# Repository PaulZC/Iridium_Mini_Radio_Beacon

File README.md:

# Iridium_Mini_Radio_Beacon

An 80g version of the [Iridium 9603N Beacon](https://github.com/PaulZC/Iridium_9603_Beacon) with eRIC4/9 radio support
.

Suitable for high altitude ballooning and many other asset tracking applications.

This version is powered by a single Energiser® Ultimate Lithium L522 (PP3) 9V battery, which helps keep the design as compact as possible.

If you want to keep the size and weight as low as possible, and don't need a radio link, have a look at
the [Iridium 9603N Mini Beacon](https://github.com/PaulZC/Iridium_9603N_Mini_Beacon) instead.

The Iridium 9603N transceiver and u-blox MAX-M8Q GNSS receiver share a single Maxtena M1600HCT-P-SMA antenna, again to keep the weight as low as possible.
The antenna sharing circuit has been flight tested on the [Iridium 9603N Solar Beacon](https://github.com/PaulZC/Iridium_9603N_Solar_Beacon).

Full details of how to track your beacon via the Rock7 RockBLOCK Gateway are included in the
[Iridium 9603N Beacon repo](https://github.com/PaulZC/Iridium_9603_Beacon/blob/master/RockBLOCK.md).

[ASSEMBLY.md](https://github.com/PaulZC/Iridium_Mini_Radio_Beacon/blob/master/ASSEMBLY.md) describes how to assemble the PCB.

The [Arduino folder](https://github.com/PaulZC/Iridium_Mini_Radio_Beacon/tree/master/Arduino) contains the code for the SAMD21 processor.
You can find the [programming instructions](https://github.com/PaulZC/Iridium_9603_Beacon/blob/master/LEARN.md#how-do-i-install-the-atsamd21g18-bootloader)
and [upload instructions](https://github.com/PaulZC/Iridium_9603_Beacon/blob/master/LEARN.md#how-do-i-upload-the-arduino-code) in the Iridium 9603N Beacon repo.

The Eagle files are available in the [Eagle folder](https://github.com/PaulZC/Iridium_Mini_Radio_Beacon/tree/master/Eagle).

The schematic, dimensions and BOM are available [here](https://github.com/PaulZC/Iridium_Mini_Radio_Beacon/blob/master/Iridium_Mini_Radio_Beacon.pdf).

The [OpenSCAD folder](https://github.com/PaulZC/Iridium_Mini_Radio_Beacon/tree/master/OpenSCAD) contains .scad and .stl files for the 3D-printed cover.

## Licence

This project is distributed under a Creative Commons Attribution + Share-alike (BY-SA) licence.
Please refer to section 5 of the licence for the "Disclaimer of Warranties and Limitation of Liability".

Enjoy!

**_Paul_**

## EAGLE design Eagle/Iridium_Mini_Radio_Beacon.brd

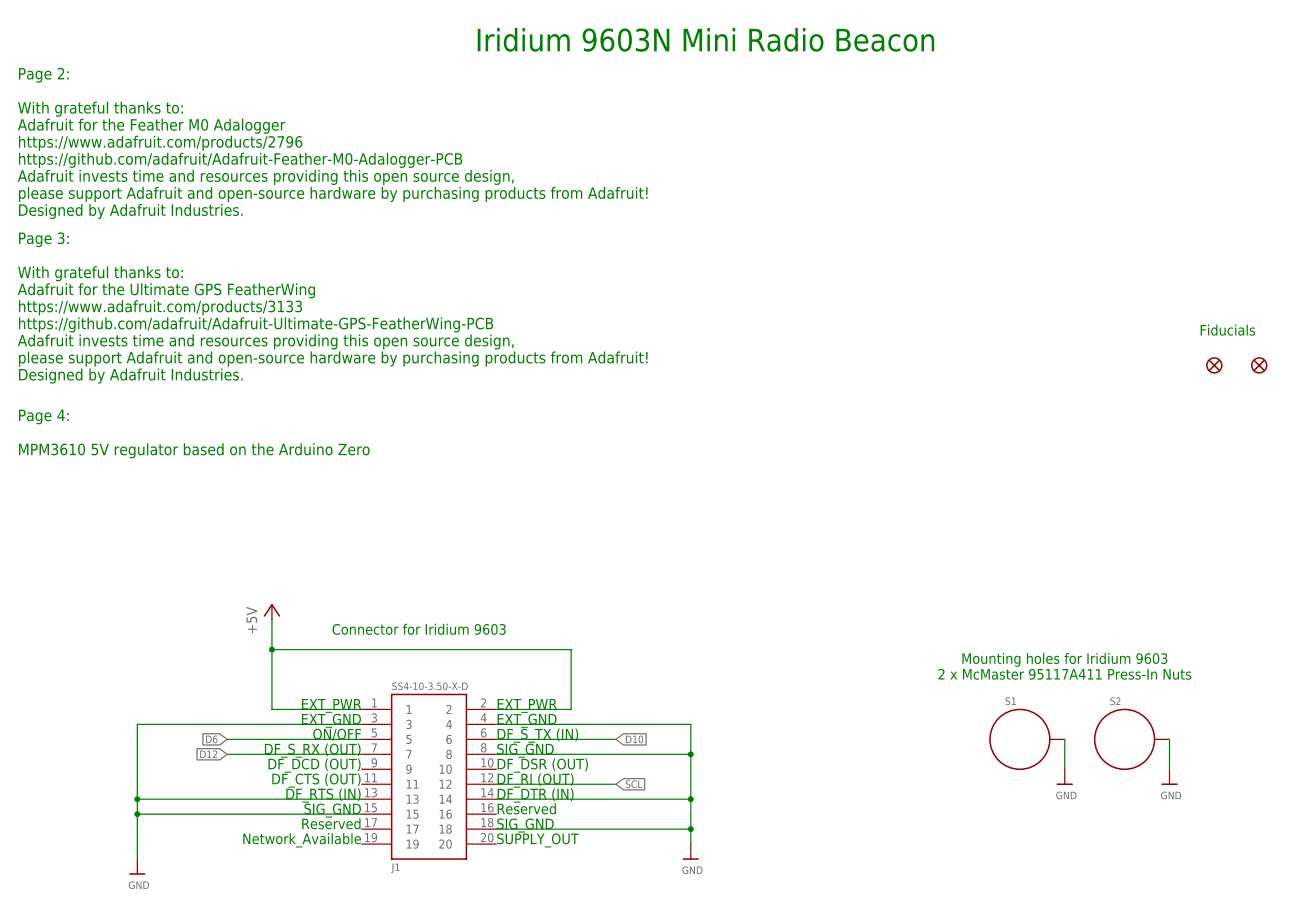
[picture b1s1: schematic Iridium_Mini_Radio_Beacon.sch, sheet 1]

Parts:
FD1, FD2: FIDUCIAL1X2; FIDUCIAL-1X2
J1: SS4-10-3.50-X-D
S1, S2: STANDOFF_ELECTRICALMCMASTER-95117A411; STANDOFF-ELECTRICAL-MCMASTER-95117A411

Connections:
+5V: J1.1, J1.2; also elsewhere on the board
D6: J1.5; also elsewhere on the board
D10: J1.6; also elsewhere on the board
D12: J1.7; also elsewhere on the board
GND: J1.3, J1.4, J1.8, J1.13, J1.14, J1.15, J1.18, S1.P1, S2.P1; also elsewhere on the board
SCL: J1.12; also elsewhere on the board

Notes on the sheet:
Connector for Iridium 9603
Mounting holes for Iridium 9603 2 x McMaster 95117A411 Press-In Nuts
Iridium 9603N Mini Radio Beacon
Page 2: With grateful thanks to: Adafruit for the Feather M0 Adalogger https://www.adafruit.com/products/2796 https://github.com/adafruit/Adafruit-Feather-M0-Adalogger-PCB Adafruit invests time and resources providing this open source design, please support Adafruit and open-source hardware by purc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
Page 3: With grateful thanks to: Adafruit for the Ultimate GPS FeatherWing https://www.adafruit.com/products/3133 https://github.com/adafruit/Adafruit-Ultimate-GPS-FeatherWing-PCB Adafruit invests time and resources providing this open source design, please support Adafruit and open-source hardware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
EXT_PWR
EXT_GND
ON/OFF
DF_S_RX (OUT)
DF_DCD (OUT)
DF_CTS (OUT)
DF_RTS (IN)
SIG_GND
Reserved
Network_Available
DF_S_TX (IN)
DF_DSR (OUT)
DF_RI (OUT)
DF_DTR (IN)
SUPPLY_OUT
Page 4: MPM3610 5V regulator based on the Arduino Zero
Fiducials

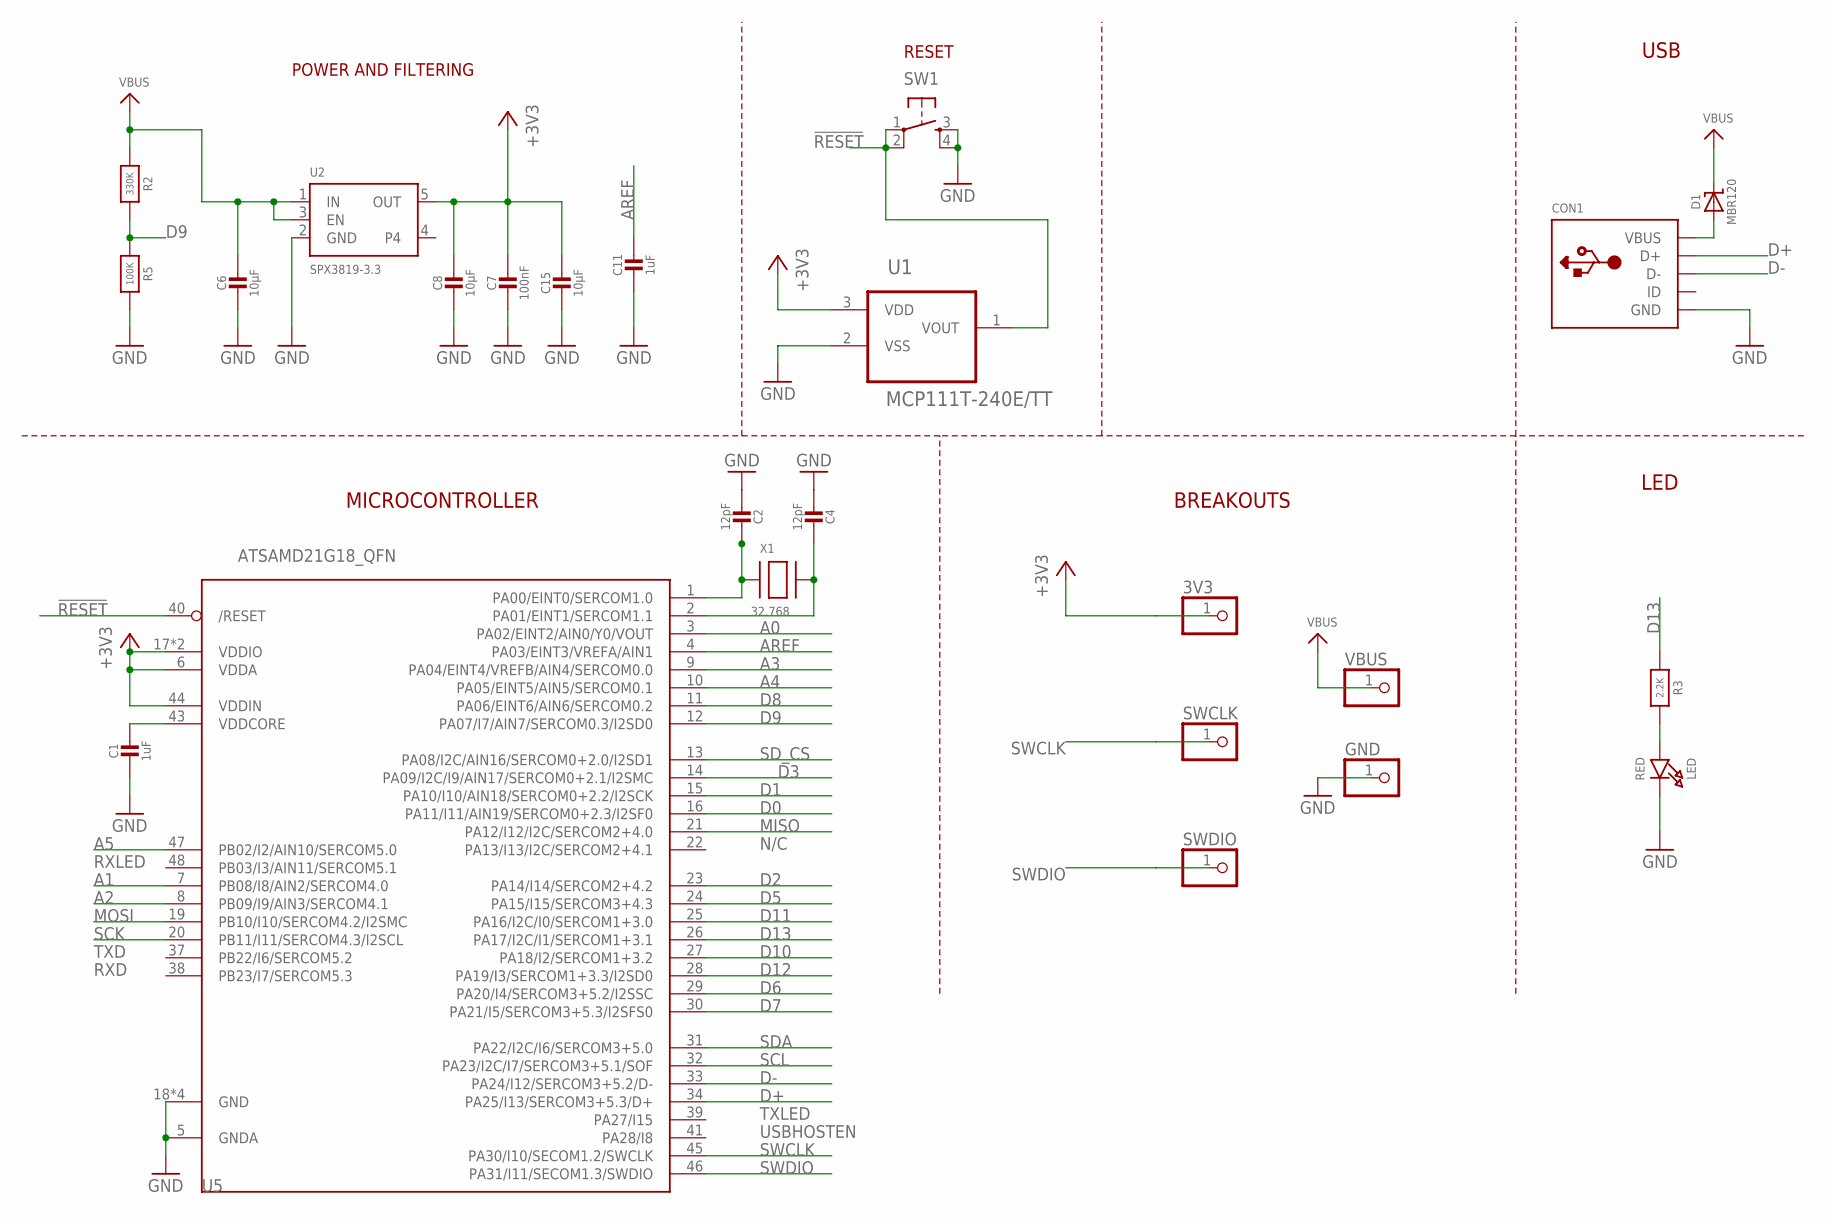
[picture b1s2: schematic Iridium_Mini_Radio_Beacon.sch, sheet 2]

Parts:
3V3: PINHD-1X1; 1X01
C1, C11: 1uF; 0603-NO
C2, C4: 12pF; 0603-NO
C6, C8, C15: 10µF; 0805-NO
C7: 100nF; 0603-NO
CON1: MICROBUILDER_USBFCI_10103594_CORRECTED; MICROBUILDER_FCI_10103594_CORRECTED
D1: MBR120; SOD-123
GND: PINHD-1X1; 1X01
LED: RED; CHIPLED_0805_NOOUTLINE
R2: 330K; 0603-NO
R3: 2.2K; 0603-NO
R5: 100K; 0603-NO
SW1: SWITCH_SPST_4_PINRECT; TACTILE_SWITCH_SMD_4.6X2.8MM
SWCLK: PINHD-1X1; 1X01
SWDIO: PINHD-1X1; 1X01
U1: MCP111T-240E/TT; SOT95P237X112-3N; MPN MCP111T-240E/TT
U2: SPX3819-3.3; SOT23-5
U5: ATSAMD21G18_QFN; TQFN48_7MM
VBUS: PINHD-1X1; 1X01
X1: 32.768; XTAL3215

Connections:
!RESET: SW1.1, SW1.2, U1.1 (VOUT), U5.40 (/RESET); also elsewhere on the board
+3V3: 3V3.1, C7.1, C8.1, C15.1, U1.3 (VDD), U2.5 (OUT), U5.6 (VDDA), U5.17 (VDDIO), U5.36 (VDDIO), U5.44 (VDDIN); also elsewhere on the board
A0: U5.3 (PA02/EINT2/AIN0/Y0/VOUT); also elsewhere on the board
A1: U5.7 (PB08/I8/AIN2/SERCOM4.0)
A2: U5.8 (PB09/I9/AIN3/SERCOM4.1); also elsewhere on the board
A3: U5.9 (PA04/EINT4/VREFB/AIN4/SERCOM0.0)
A4: U5.10 (PA05/EINT5/AIN5/SERCOM0.1)
A5: U5.47 (PB02/I2/AIN10/SERCOM5.0)
AREF: C11.1, U5.4 (PA03/EINT3/VREFA/AIN1)
D0: U5.16 (PA11/I11/AIN19/SERCOM0+2.3/I2SF0); also elsewhere on the board
D1: U5.15 (PA10/I10/AIN18/SERCOM0+2.2/I2SCK); also elsewhere on the board
D2: U5.23 (PA14/I14/SERCOM2+4.2)
D3: U5.14 (PA09/I2C/I9/AIN17/SERCOM0+2.1/I2SMC)
D5: U5.24 (PA15/I15/SERCOM3+4.3); also elsewhere on the board
D6: U5.29 (PA20/I4/SERCOM3+5.2/I2SSC); also elsewhere on the board
D7: U5.30 (PA21/I5/SERCOM3+5.3/I2SFS0)
D8: U5.11 (PA06/EINT6/AIN6/SERCOM0.2)
D9: R2.2, R5.1, U5.12 (PA07/I7/AIN7/SERCOM0.3/I2SD0)
D10: U5.27 (PA18/I2/SERCOM1+3.2); also elsewhere on the board
D11: U5.25 (PA16/I2C/I0/SERCOM1+3.0); also elsewhere on the board
D12: U5.28 (PA19/I3/SERCOM1+3.3/I2SD0); also elsewhere on the board
D13: R3.1, U5.26 (PA17/I2C/I1/SERCOM1+3.1)
D+: CON1.D+, U5.34 (PA25/I13/SERCOM3+5.3/D+)
D-: CON1.D-, U5.33 (PA24/I12/SERCOM3+5.2/D-)
GND: C1.2, C2.2, C4.2, C6.2, C7.2, C8.2, C11.2, C15.2, CON1.BASE@1 (GND), CON1.BASE@2 (GND), CON1.GND, CON1.SPRT@1 (GND), CON1.SPRT@2 (GND), CON1.SPRT@3 (GND), CON1.SPRT@4 (GND), GND.1, LED.C, R5.2, SW1.3, SW1.4, U1.2 (VSS), U2.2 (GND), U5.5 (GNDA), U5.18 (GND), U5.35 (GND), U5.42 (GND), U5.THERMAL (GND); also elsewhere on the board
MISO: U5.21 (PA12/I12/I2C/SERCOM2+4.0)
MOSI: U5.19 (PB10/I10/SERCOM4.2/I2SMC); also elsewhere on the board
unnamed: LED.A, R3.2
unnamed: C2.1, U5.1 (PA00/EINT0/SERCOM1.0), X1.P$1
unnamed: C4.1, U5.2 (PA01/EINT1/SERCOM1.1), X1.P$2
unnamed: CON1.VBUS, D1.A
SCK: U5.20 (PB11/I11/SERCOM4.3/I2SCL); also elsewhere on the board
SCL: U5.32 (PA23/I2C/I7/SERCOM3+5.1/SOF); also elsewhere on the board
SDA: U5.31 (PA22/I2C/I6/SERCOM3+5.0)
SD_CS: U5.13 (PA08/I2C/AIN16/SERCOM0+2.0/I2SD1)
SWCLK: SWCLK.1, U5.45 (PA30/I10/SECOM1.2/SWCLK)
SWDIO: SWDIO.1, U5.46 (PA31/I11/SECOM1.3/SWDIO)
VBUS: C6.1, D1.C, R2.1, U2.1 (IN), U2.3 (EN), VBUS.1; also elsewhere on the board
VDDCORE1: C1.1, U5.43 (VDDCORE)

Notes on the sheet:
POWER AND FILTERING
RESET
N/C
TXLED
USBHOSTEN
RXLED
TXD
RXD
USB
BREAKOUTS
LED
MICROCONTROLLER

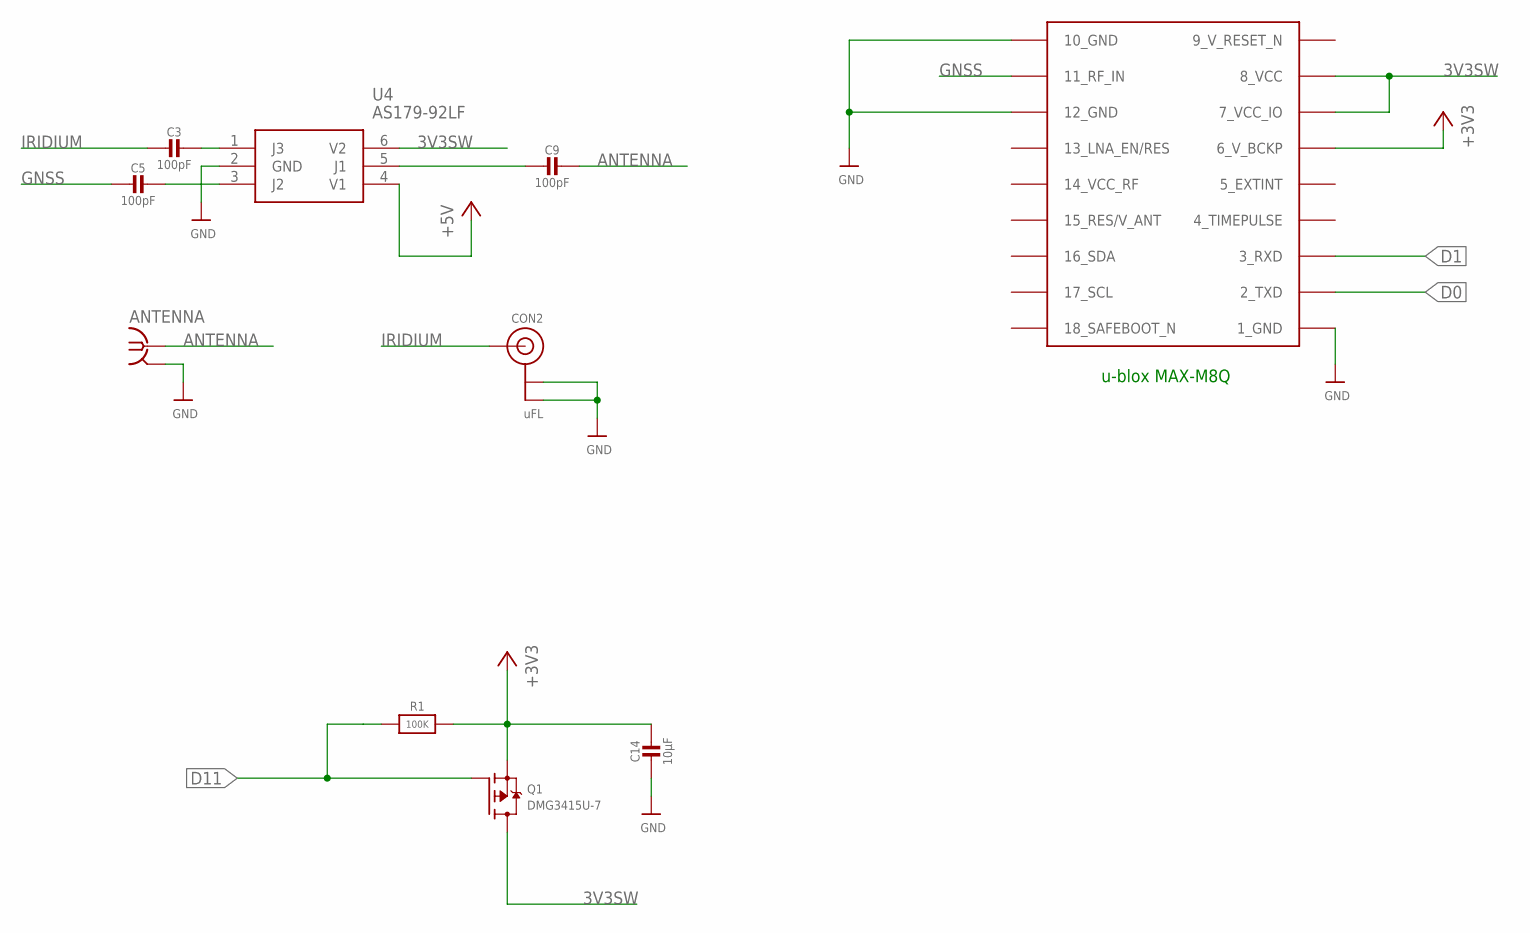
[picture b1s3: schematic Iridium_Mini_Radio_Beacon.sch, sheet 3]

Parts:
ANTENNA: SMA-142-0711-821/826; J502-ND-142-0711-821/826
C3, C5, C9: 100pF; 0603-NO
C14: 10µF; 0805-NO
CON2: uFL; U.FL
Q1: DMG3415U-7; SOT23-WIDE
R1: 100K; 0603-NO
U3: MAX-M8
U4: AS179-92LF; SOT65P220X100-6N

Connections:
3V3SW: Q1.3 (D), U3.7_VCC_IO, U3.8_VCC, U4.6 (V2)
9_V_RESET_N: U3.9_RESET_N (9_V_RESET_N)
+3V3: C14.1, Q1.2 (S), R1.2, U3.6_V_BCKP; also elsewhere on the board
+5V: U4.4 (V1); also elsewhere on the board
ANTENNA: ANTENNA.1, C9.1
D0: U3.2_TXD; also elsewhere on the board
D1: U3.3_RXD; also elsewhere on the board
D11: Q1.1 (G), R1.1; also elsewhere on the board
GND: ANTENNA.G@1 (2), ANTENNA.G@2 (2), ANTENNA.G@3 (2), ANTENNA.G@4 (2), C14.2, CON2.1 (GND), CON2.2 (GND), U3.1_GND, U3.10_GND, U3.12_GND, U4.2 (GND); also elsewhere on the board
GNSS: C5.2, U3.11_RF_IN
IRIDIUM: C3.2, CON2.3 (SIGNAL)
unnamed: C3.1, U4.1 (J3)
unnamed: C5.1, U4.3 (J2)
unnamed: C9.2, U4.5 (J1)

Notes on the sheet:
u-blox MAX-M8Q

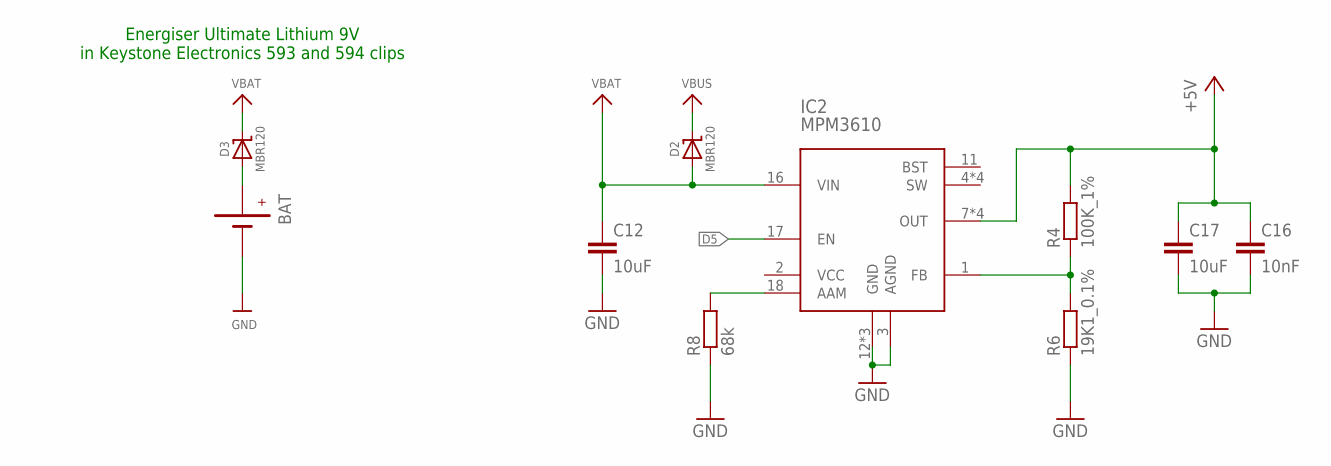
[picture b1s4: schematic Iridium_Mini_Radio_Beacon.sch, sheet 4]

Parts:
BAT: BATTERYBATTERY-9V-KEYSTONE-593-594-FLIPPED; BATTERY-9V-KEYSTONE-593-594-FLIPPED
C12, C17: 10uF; C0805
C16: 10nF; C0805
D2, D3: MBR120; SOD-123
IC2: MPM3610; QFN-20
R4: 100K_1%; R0603
R6: 19K1_0.1%; R0603
R8: 68k; R0603

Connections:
+5V: C16.1, C17.1, IC2.7 (OUT), IC2.8 (OUT), IC2.9 (OUT), IC2.20 (OUT), R4.2; also elsewhere on the board
D5: IC2.17 (EN); also elsewhere on the board
GND: BAT.GND (-), BAT.GND1 (-), BAT.GND2 (-), C12.2, C16.2, C17.2, IC2.3 (AGND), IC2.12 (GND), IC2.13 (GND), IC2.14 (GND), R6.1, R8.1; also elsewhere on the board
unnamed: BAT.PWR (+), BAT.PWR1 (+), BAT.PWR2 (+), D3.A
unnamed: IC2.1 (FB), R4.1, R6.2
unnamed: IC2.18 (AAM), R8.2
VBAT: C12.1, D2.A, D3.C, IC2.16 (VIN)
VBUS: D2.C; also elsewhere on the board

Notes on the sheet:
Energiser Ultimate Lithium 9V in Keystone Electronics 593 and 594 clips

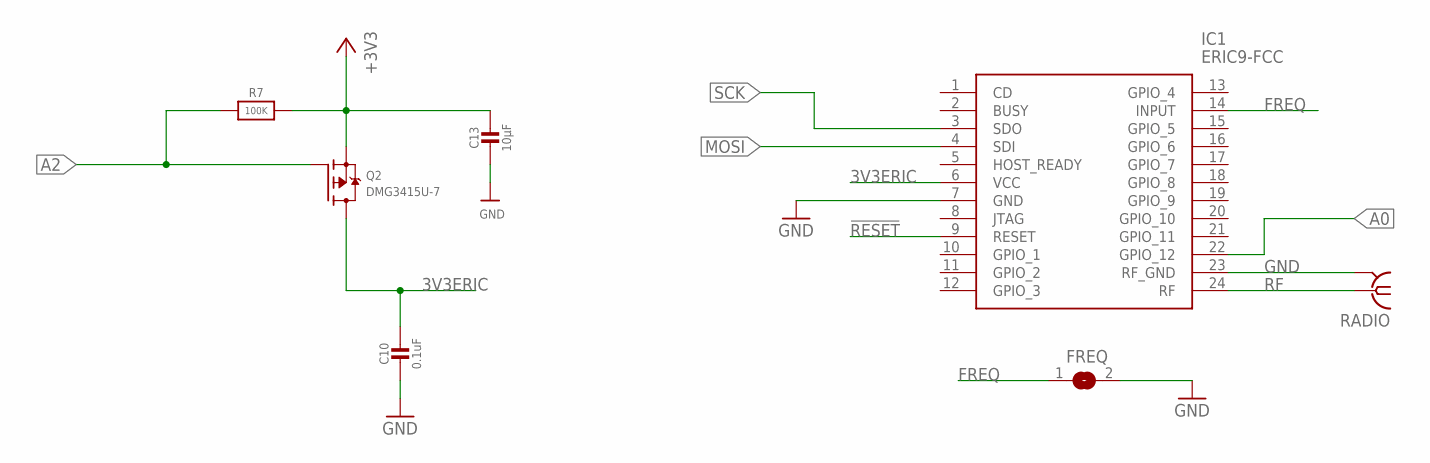
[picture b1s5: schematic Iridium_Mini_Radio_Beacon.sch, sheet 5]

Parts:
C10: 0.1uF; 0603-NO
C13: 10µF; 0805-NO
FREQ: SOLDERJUMPER; SOLDERJUMPER_ARROW_NOPASTE
IC1: ERIC9-FCC; ERIC4
Q2: DMG3415U-7; SOT23-WIDE
R7: 100K; 0603-NO
RADIO: SMA-142-0711-821/826; J502-ND-142-0711-821/826

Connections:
3V3ERIC: C10.1, IC1.6 (VCC), Q2.3 (D)
!RESET: IC1.9 (RESET); also elsewhere on the board
+3V3: C13.1, Q2.2 (S), R7.2; also elsewhere on the board
A0: IC1.22 (GPIO_12); also elsewhere on the board
A2: Q2.1 (G), R7.1; also elsewhere on the board
FREQ: FREQ.1, IC1.14 (INPUT)
GND: C10.2, C13.2, FREQ.2, IC1.7 (GND), IC1.23 (RF_GND), RADIO.G@1 (2), RADIO.G@2 (2), RADIO.G@3 (2), RADIO.G@4 (2); also elsewhere on the board
MOSI: IC1.4 (SDI); also elsewhere on the board
RF: IC1.24 (RF), RADIO.1
SCK: IC1.3 (SDO); also elsewhere on the board

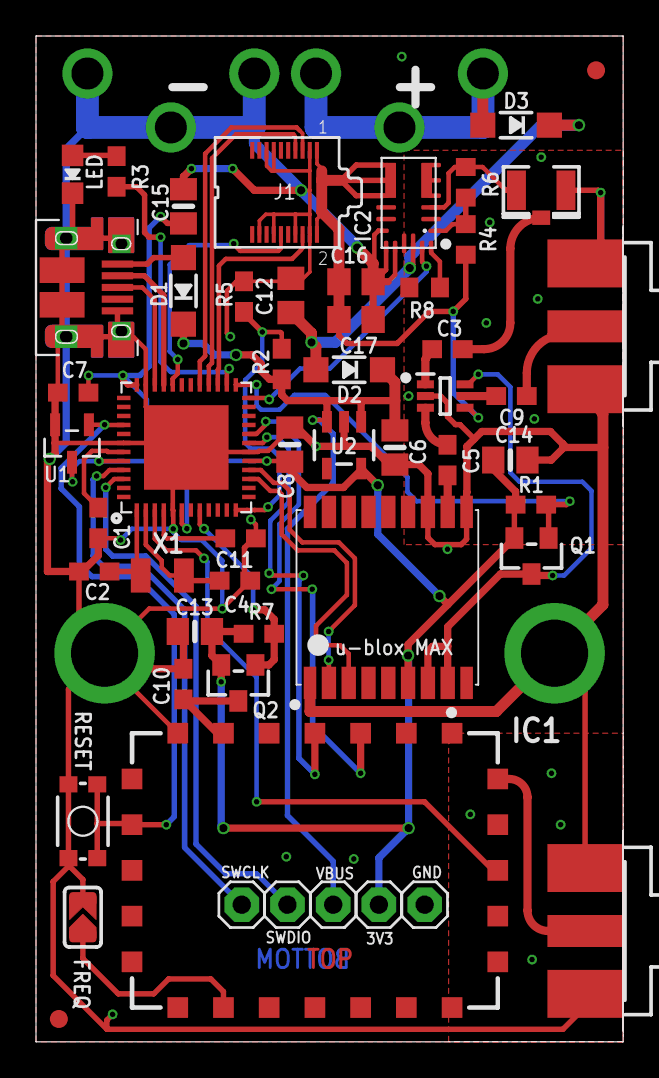
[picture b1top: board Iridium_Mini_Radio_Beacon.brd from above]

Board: 2 copper layers, 32.6 x 55.9 mm, 56 parts (1 on the bottom side), 43 nets.

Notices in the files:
parts and their libraries:
microbuilder: This work is placed in the public domain, and may be freely used for commercial and non-commercial work with the following conditions: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
SparkFun-Electromechanical: Licensing: Creative Commons ShareAlike 4.0 International - https://creativecommons.org/licenses/by-sa/4.0
